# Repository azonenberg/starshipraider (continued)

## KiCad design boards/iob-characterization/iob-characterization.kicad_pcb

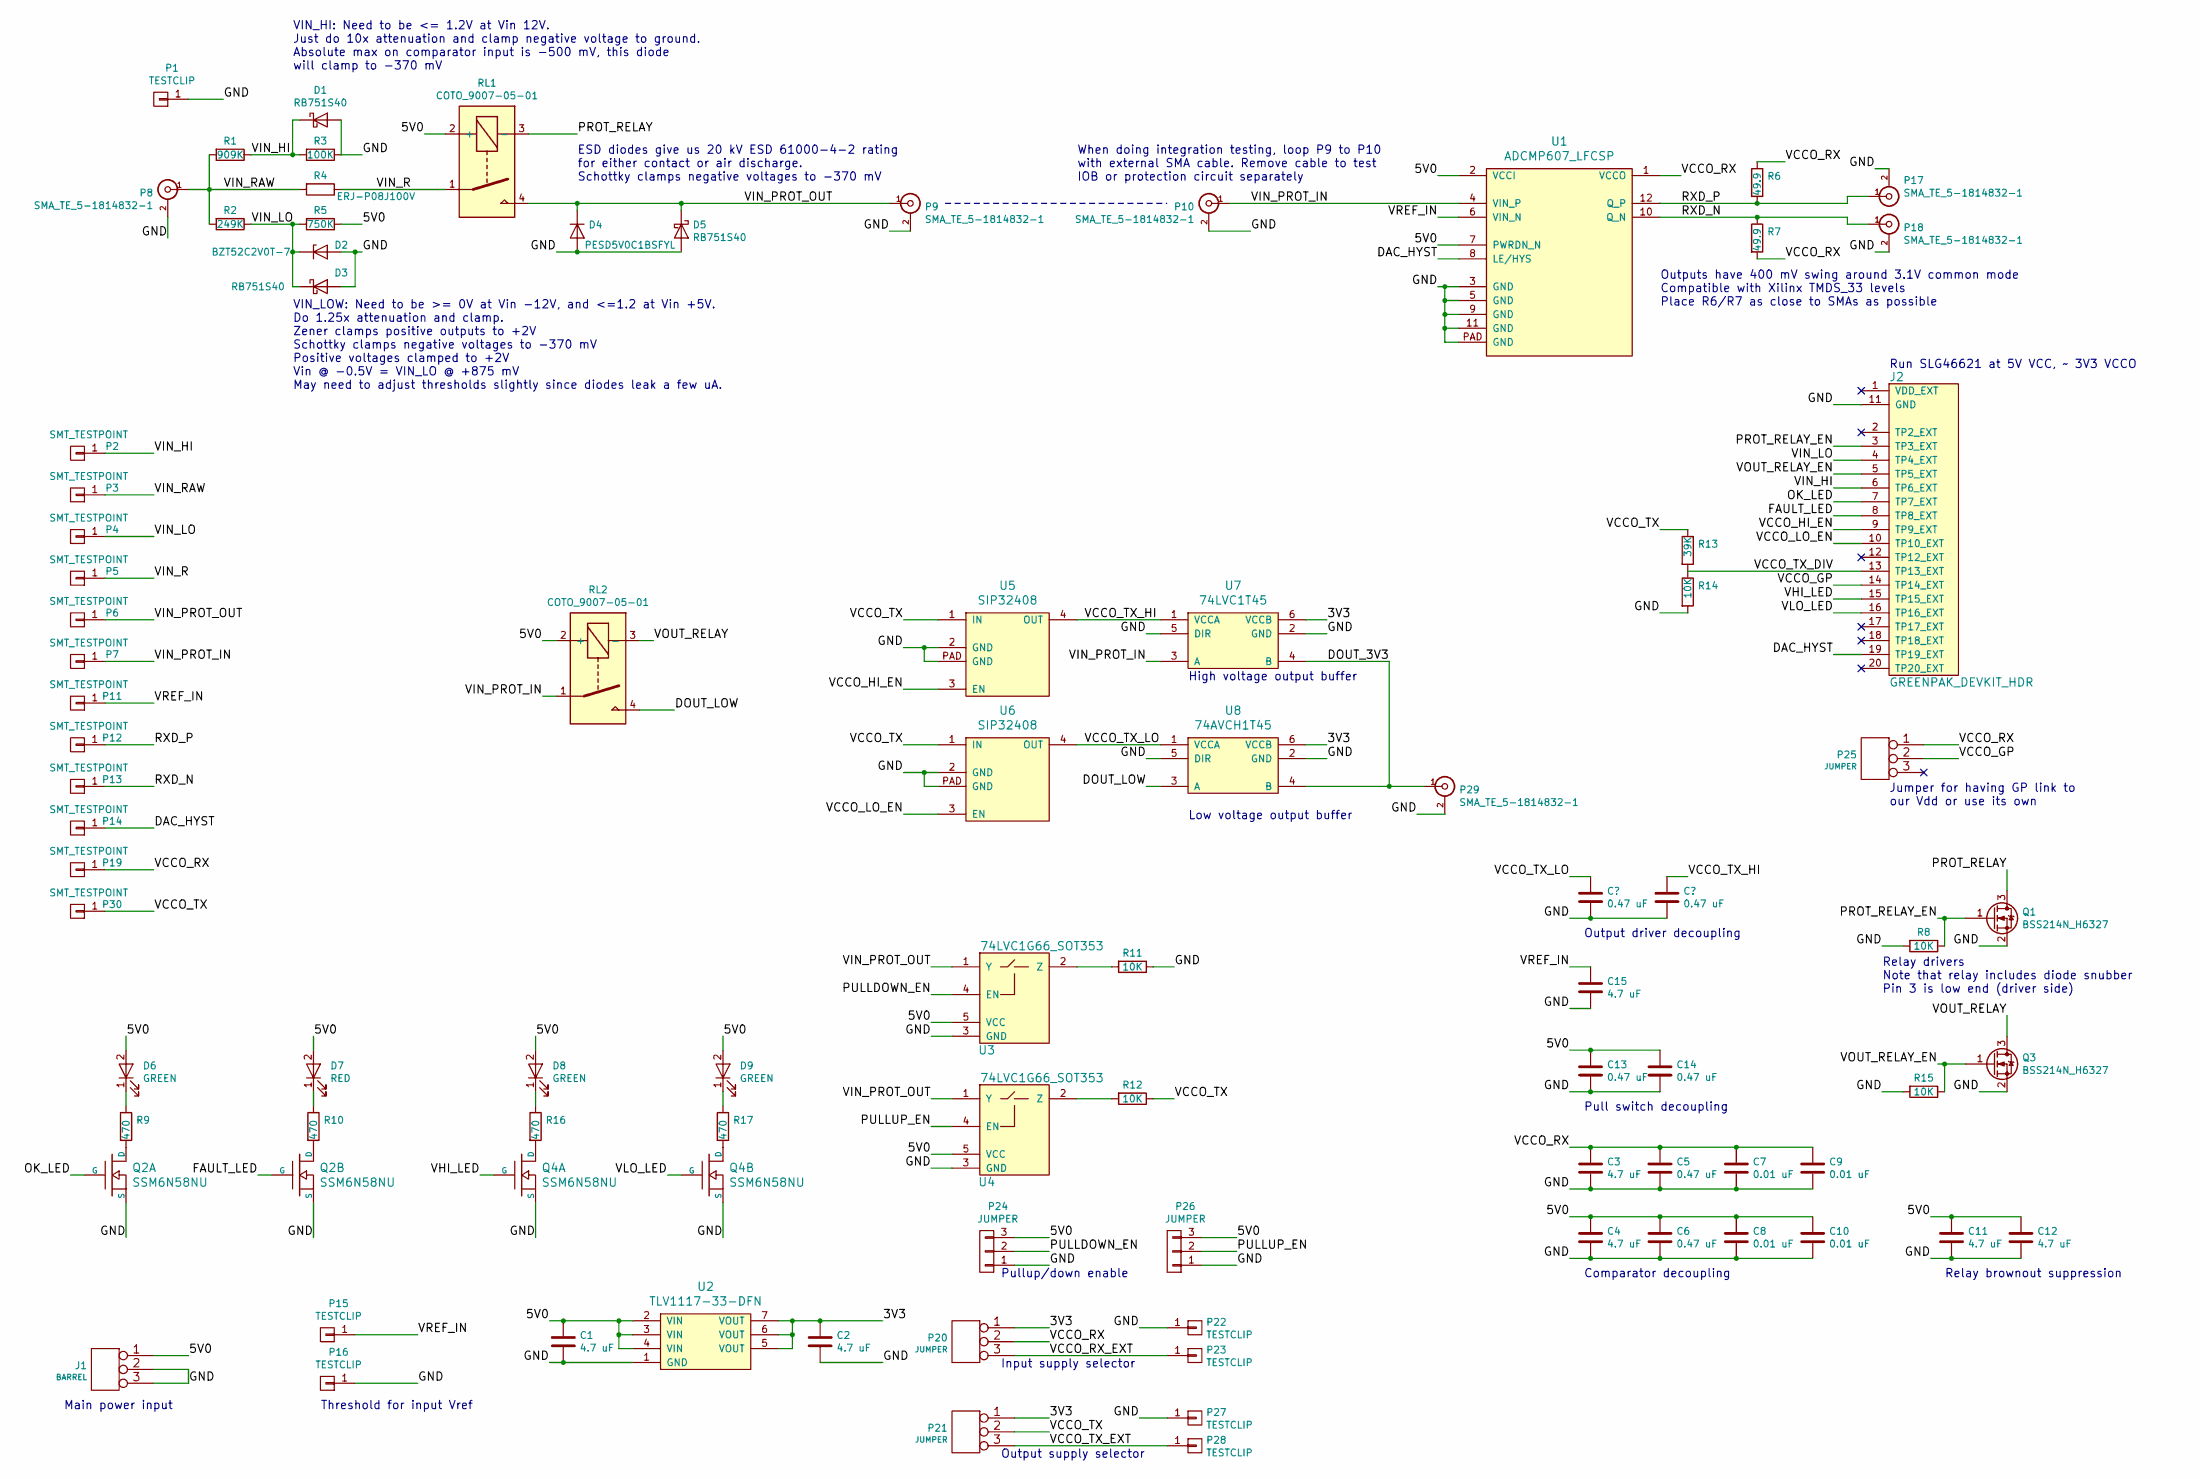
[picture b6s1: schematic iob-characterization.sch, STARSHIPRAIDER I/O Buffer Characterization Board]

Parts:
C1, C2, C3, C4, C11, C12, C15: 4.7 uF; EIA_0603_CAP_NOSILK
C5, C6, C13, C14: 0.47 uF; EIA_0402_CAP_NOSILK
C7, C8, C9, C10: 0.01 uF; EIA_0402_CAP_NOSILK
D1, D3, D5: RB751S40; SOD523F
D2: BZT52C2V0T-7; SOD523
D4: PESD5V0C1BSFYL; SOD962_2
D6, D8, D9: GREEN; EIA_0603_LED
D7: RED; EIA_0603_LED
J1: BARREL; CONN_CUI_PJ-058BH_HIPWR_BARREL_NOSLOT
J2: GREENPAK_DEVKIT_HDR; CONN_HEADER_2.54MM_2x10_RA_FEMALE
P1, P15, P16, P22, P23, P27, P28: TESTCLIP; TESTPOINT_SMT_KEYSTONE_5016
P2, P3, P4, P5, P6, P7, P11, P12, P13, P14, P19, P30: SMT_TESTPOINT; TESTPOINT_SMT_0.5MM
P8, P9, P10, P17, P18, P29: SMA_TE_5-1814832-1; CONN_SMA_PTH
P20, P21, P24, P25, P26: JUMPER; CONN_HEADER_2.54MM_1x3
Q1, Q3: BSS214N_H6327; SOT23_3
Q2, Q4: SSM6N58NU; DFN_6_0.65MM_2x2MM_GDS
R1: 909K; EIA_0402_RES_NOSILK
R2: 249K; EIA_0402_RES_NOSILK
R3: 100K; EIA_0402_RES_NOSILK
R4: ERJ-P08J100V; EIA_1206_CAP_NOSILK
R5: 750K; EIA_0402_RES_NOSILK
R6, R7: 49.9; EIA_0402_RES_NOSILK
R8, R11, R12, R14, R15: 10K; EIA_0402_RES_NOSILK
R9, R10, R16, R17: 470; EIA_0402_RES_NOSILK
R13: 39K; EIA_0402_RES_NOSILK
RL1, RL2: COTO_9007-05-01; RELAY_COTO_9007
U1: ADCMP607_LFCSP; QFN_12_0.5MM_3x3MM
U2: TLV1117-33-DFN; DFN_8_0.8MM_4x4MM
U3, U4: 74LVC1G66_SOT353; SOT353_1
U5, U6: SIP32408; DFN_4_0.5MM_1.6x1.2MM
U7: 74LVC1T45; SOT363
U8: 74AVCH1T45; SOT363

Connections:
/3V3: C2.1, P20.1, P21.1, U2.5 (VOUT), U2.6 (VOUT), U2.7 (VOUT), U7.6 (VCCB), U8.6 (VCCB)
/5V0: C1.1, C4.1, C6.1, C8.1, C10.1, C11.1, C12.1, C13.1, C14.1, D6.2 (A), D7.2 (A), D8.2 (A), D9.2 (A), J1.1, P24.3, P26.3, R5.1, RL1.2 (+), RL2.2 (+), U1.2 (VCCI), U1.7 (PWRDN_N), U2.2 (VIN), U2.3 (VIN), U2.4 (VIN), U3.5 (VCC), U4.5 (VCC)
/DAC_HYST: J2.19 (TP19_EXT), P14.1, U1.8 (LE/HYS)
/DOUT_3V3: P29.1 (In), U7.4 (B), U8.4 (B)
/DOUT_LOW: RL2.4, U8.3 (A)
/FAULT_LED: J2.8 (TP8_EXT), Q2.G2 (G)
/GND: C1.2, C2.2, C3.2, C4.2, C5.2, C6.2, C7.2, C8.2, C9.2, C10.2, C11.2, C12.2, C13.2, C14.2, C15.2, D1.2 (A), D2.2 (A), D3.2 (A), D4.2 (A), D5.2 (A), J1.2 (PM), J1.3, J2.11 (GND), P1.1, P8.2 (Ext), P9.2 (Ext), P10.2 (Ext), P16.1, P17.2 (Ext), P18.2 (Ext), P22.1, P24.1, P26.1, P27.1, P29.2 (Ext), Q1.2 (S), Q2.S1 (S), Q2.S2 (S), Q3.2 (S), Q4.S1 (S), Q4.S2 (S), R3.1, R8.2, R11.1, R14.2, R15.2, U1.3 (GND), U1.5 (GND), U1.9 (GND), U1.11 (GND), U1.PAD (GND), U2.1 (GND), U3.3 (GND), U4.3 (GND), U5.2 (GND), U5.PAD (GND), U6.2 (GND), U6.PAD (GND), U7.2 (GND), U7.5 (DIR), U8.2 (GND), U8.5 (DIR); also elsewhere on the board
/OK_LED: J2.7 (TP7_EXT), Q2.G1 (G)
/PROT_RELAY: Q1.3 (D), RL1.3 (-)
/PROT_RELAY_EN: J2.3 (TP3_EXT), Q1.1 (G), R8.1
/PULLDOWN_EN: P24.2, U3.4 (EN)
/PULLUP_EN: P26.2, U4.4 (EN)
/RXD_N: P13.1, P18.1 (In), R7.1, U1.10 (Q_N)
/RXD_P: P12.1, P17.1 (In), R6.2, U1.12 (Q_P)
/VCCO_GP: J2.14 (TP14_EXT), P25.2 (PM)
/VCCO_HI_EN: J2.9 (TP9_EXT), U5.3 (EN)
/VCCO_LO_EN: J2.10 (TP10_EXT), U6.3 (EN)
/VCCO_RX: C3.1, C5.1, C7.1, C9.1, P19.1, P20.2 (PM), P25.1, R6.1, R7.2, U1.1 (VCCO)
/VCCO_RX_EXT: P20.3, P23.1
/VCCO_TX: P21.2 (PM), P30.1, R12.1, R13.1, U5.1 (IN), U6.1 (IN)
/VCCO_TX_DIV: J2.13 (TP13_EXT), R13.2, R14.1
/VCCO_TX_EXT: P21.3, P28.1
/VCCO_TX_HI: U5.4 (OUT), U7.1 (VCCA); also elsewhere on the board
/VCCO_TX_LO: U6.4 (OUT), U8.1 (VCCA); also elsewhere on the board
/VHI_LED: J2.15 (TP15_EXT), Q4.G1 (G)
/VIN_HI: D1.1 (K), J2.6 (TP6_EXT), P2.1, R1.1, R3.2
/VIN_LO: D2.1 (K), D3.1 (K), J2.4 (TP4_EXT), P4.1, R2.1, R5.2
/VIN_PROT_IN: P7.1, P10.1 (In), RL2.1, U1.4 (VIN_P), U7.3 (A)
/VIN_PROT_OUT: D4.1 (K), D5.1 (K), P6.1, P9.1 (In), RL1.4, U3.1 (Y), U4.1 (Y)
/VIN_R: P5.1, R4.1, RL1.1
/VIN_RAW: P3.1, P8.1 (In), R1.2, R2.2, R4.2
/VLO_LED: J2.16 (TP16_EXT), Q4.G2 (G)
/VOUT_RELAY: Q3.3 (D), RL2.3 (-)
/VOUT_RELAY_EN: J2.5 (TP5_EXT), Q3.1 (G), R15.1
/VREF_IN: C15.1, P11.1, P15.1, U1.6 (VIN_N)
unnamed: D6.1 (K), R9.1
unnamed: D7.1 (K), R10.1
unnamed: D8.1 (K), R16.1
unnamed: D9.1 (K), R17.1
unnamed: Q2.D1 (D), R9.2
unnamed: Q2.D2 (D), R10.2
unnamed: Q4.D1 (D), R16.2
unnamed: Q4.D2 (D), R17.2
unnamed: R11.2, U3.2 (Z)
unnamed: R12.2, U4.2 (Z)

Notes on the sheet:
VIN_HI: Need to be <= 1.2V at Vin 12V. Just do 10x attenuation and clamp negative voltage to ground. Absolute max on comparator input is -500 mV, this diode will clamp to -370 mV
VIN_LOW: Need to be >= 0V at Vin -12V, and <=1.2 at Vin +5V. Do 1.25x attenuation and clamp. Zener clamps positive outputs to +2V Schottky clamps negative voltages to -370 mV Positive voltages clamped to +2V Vin @ -0.5V = VIN_LO @ +875 mV May need to adjust thresholds slightly since diodes leak a f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
ESD diodes give us 20 kV ESD 61000-4-2 rating for either contact or air discharge. Schottky clamps negative voltages to -370 mV
When doing integration testing, loop P9 to P10 with external SMA cable. Remove cable to test IOB or protection circuit separately
Outputs have 400 mV swing around 3.1V common mode Compatible with Xilinx TMDS_33 levels Place R6/R7 as close to SMAs as possible
Main power input
Threshold for input Vref
Run SLG46621 at 5V VCC, ~~ 3V3 VCCO
Jumper for having GP link to our Vdd or use its own
Relay drivers Note that relay includes diode snubber Pin 3 is low end (driver side)
Comparator decoupling
Relay brownout suppression
Output supply selector
Input supply selector
Pullup/down enable
Pull switch decoupling
Low voltage output buffer
High voltage output buffer
Output driver decoupling

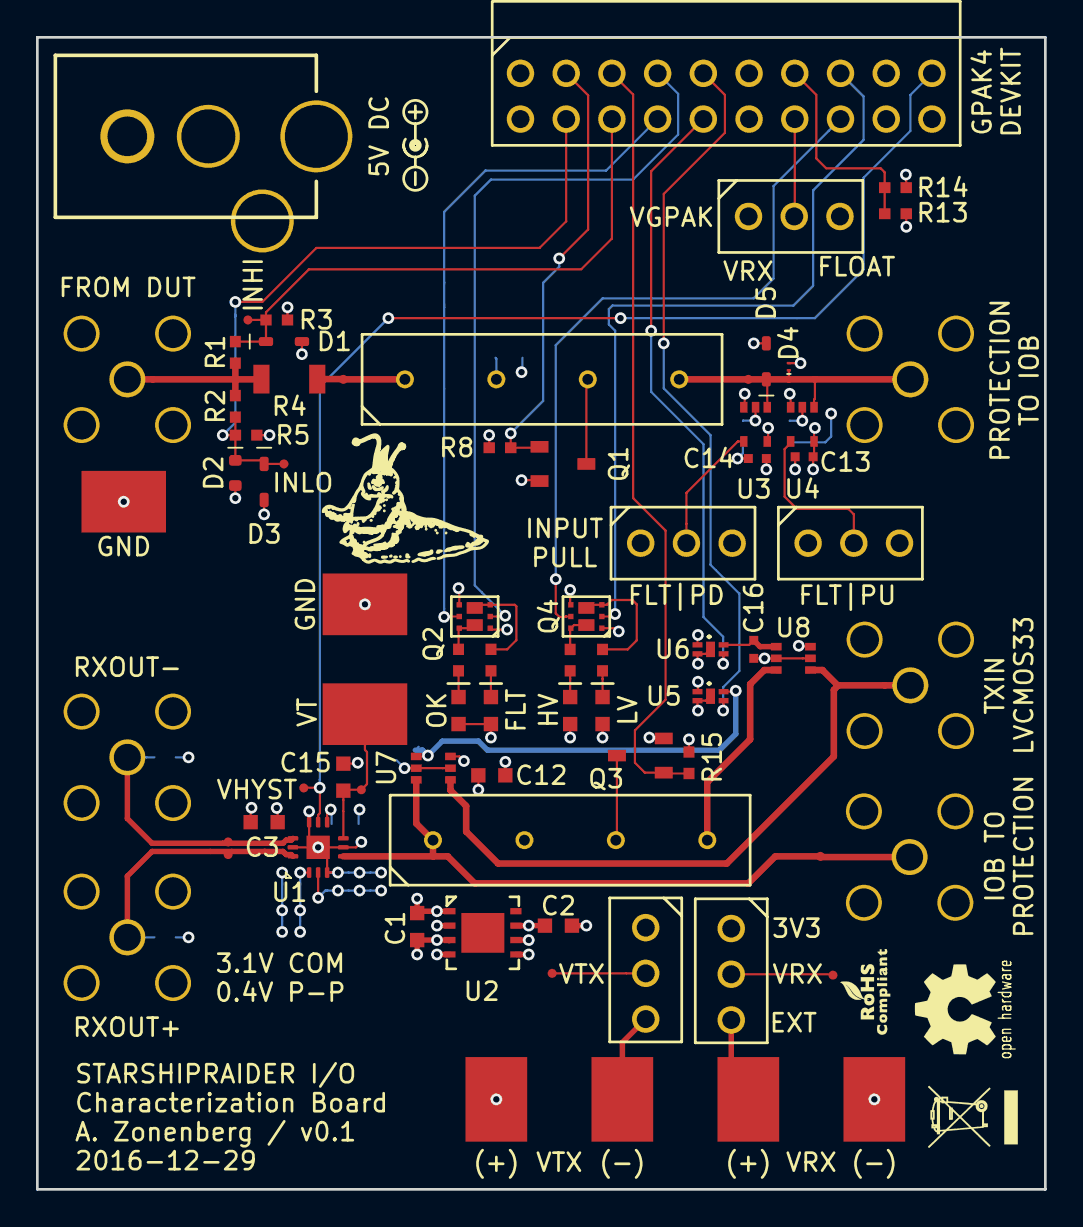
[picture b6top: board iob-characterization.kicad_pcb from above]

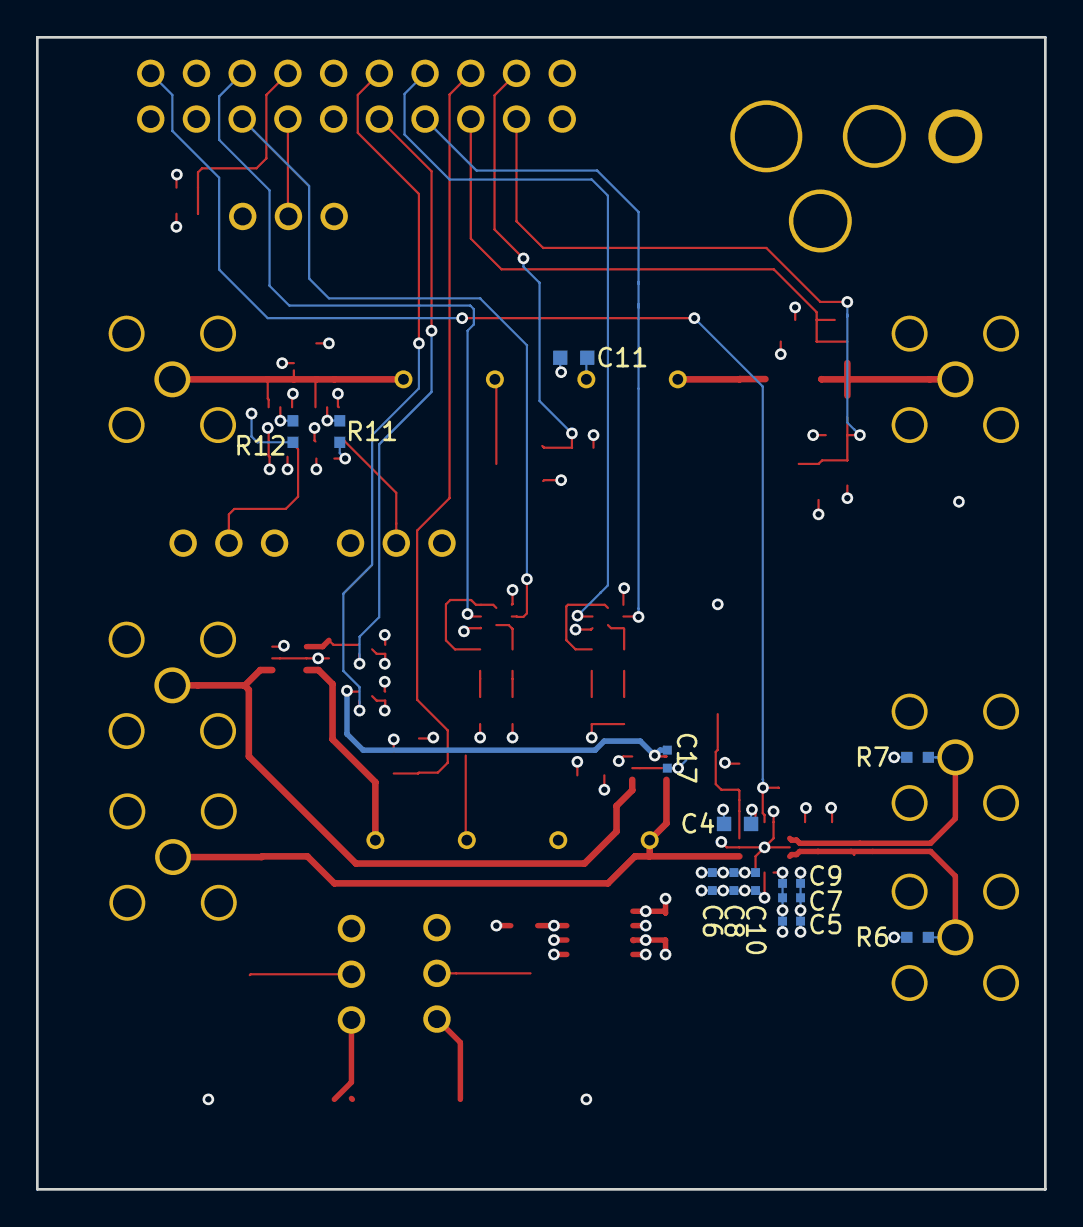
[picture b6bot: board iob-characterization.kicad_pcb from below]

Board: 4 copper layers, 56.0 x 64.0 mm, 89 parts (13 on the bottom side), 45 nets.

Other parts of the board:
C16, C17: 0.47 uF; EIA_0402_CAP_NOSILK

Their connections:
/GND: C16.2, C17.2; also elsewhere on the board
/VCCO_TX_HI: C17.1; also elsewhere on the board
/VCCO_TX_LO: C16.1; also elsewhere on the board

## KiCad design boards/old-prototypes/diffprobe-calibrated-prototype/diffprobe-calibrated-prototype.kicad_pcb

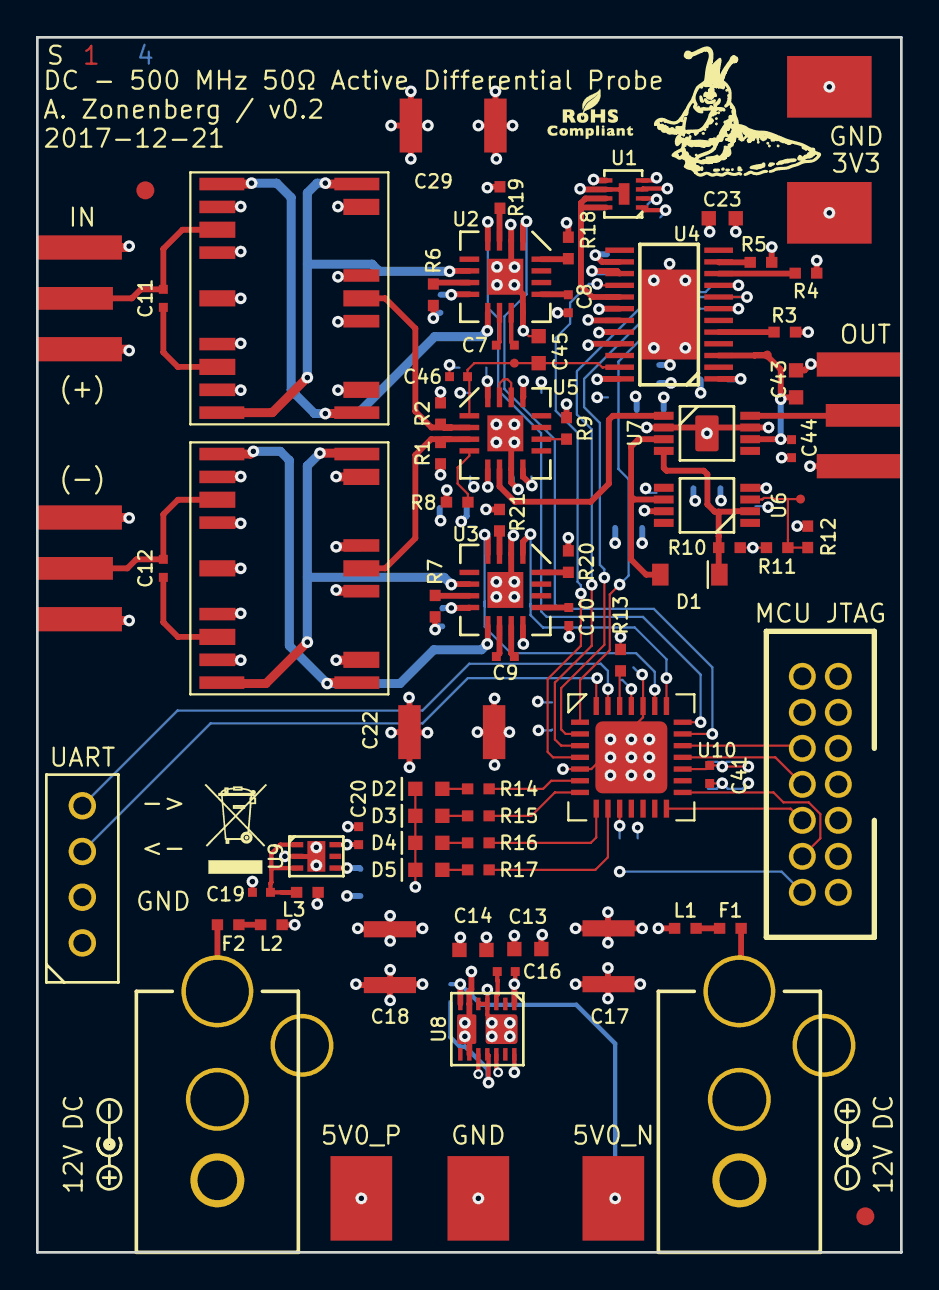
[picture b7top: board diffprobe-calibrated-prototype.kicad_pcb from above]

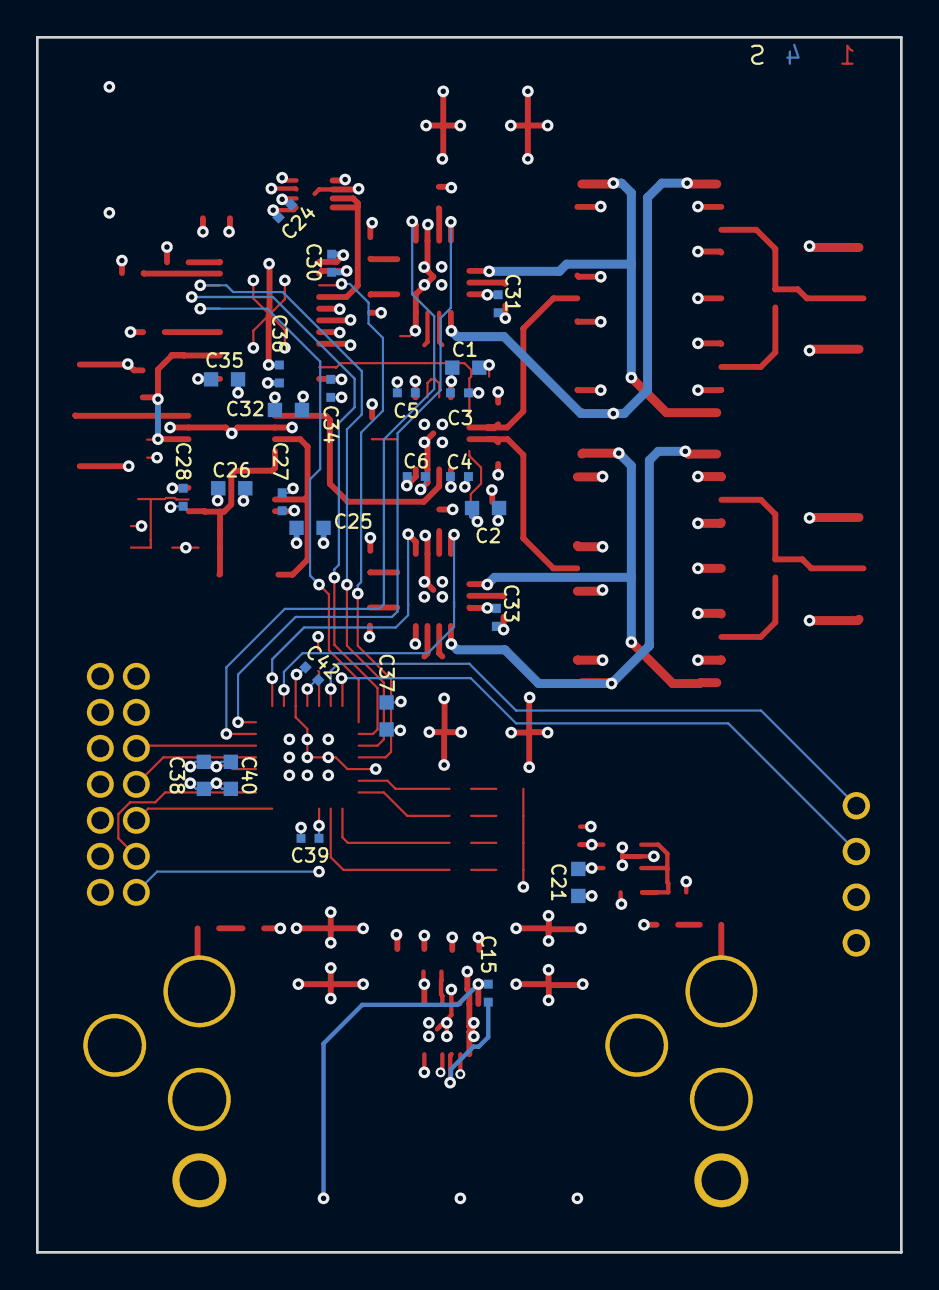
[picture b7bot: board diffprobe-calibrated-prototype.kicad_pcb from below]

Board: 4 copper layers, 48.0 x 67.5 mm, 106 parts (25 on the bottom side), 74 nets.

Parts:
C1, C2, C21, C23, C25, C26, C32, C35, C37, C38, C40, C43, C45: 4.7 uF; EIA_0603_CAP_NOSILK
C3, C4, C5, C6, C24, C27, C28, C30, C34, C36, C39, C41, C42, C44, C46: 0.47 uF; EIA_0402_CAP_NOSILK
C7, C8, C9, C10, C31, C33: 0.1 uF 25V; EIA_0402_CAP_NOSILK
C11, C12, C20: 0.1 uF; EIA_0402_CAP_NOSILK
C13, C14: 4.7 uF 10V; EIA_0603_CAP_NOSILK
C15, C16: 0.01 uF; EIA_0402_CAP_NOSILK
C17, C18: 10 uF 25V; EIA_1210_CAP_NOSILK
C19: 1 uF; EIA_0402_CAP_NOSILK
C22, C29: 22 uF 25V; EIA_1812_CAP_NOSILK
D1: 1N4148; SOD123
D2, D3, D4, D5: GREEN; EIA_0603_LED
F1, F2: 250 mA; EIA_0402_RES_NOSILK
FIDUCIAL_1MM, FIDUCIAL_1MM#2: VAL**; FIDUCIAL_1MM
J1: XILINX_JTAG; XILINX_JTAG_PTH_MOLEX_0878311420
J2, J3: CUI PJ-058BH; CONN_CUI_PJ-058BH_HIPWR_BARREL_NOSLOT
J4, J5, J6: SMA; CONN_SMA_EDGE_SAMTEC_SMA_J_P_H_ST_EM1
J7: CONN_01X04; CONN_HEADER_2.54MM_1x4
K1, K2: AXICOM_HF3_2COIL; RELAY_TE_HF3_2COIL_50OHM
L1, L2, L3: BLM15PX471SN1D; EIA_0402_RES_NOSILK
P4, P5, P6, P7, P8: TESTCLIP; TESTPOINT_SMT_KEYSTONE_5016
R1, R2: 49.9; EIA_0402_RES_NOSILK
R3, R4, R5, R8, R9, R18, R19, R20, R21: 0; EIA_0402_RES_NOSILK
R6, R7: 2; EIA_0402_RES_NOSILK
R10, R11: 3.9K; EIA_0402_RES_NOSILK
R12: 499; EIA_0402_RES_NOSILK
R13: 1K; EIA_0402_RES_NOSILK
R14, R15, R16, R17: 470; EIA_0402_RES_NOSILK
TP1, TP2, TP3: CONN_01X01; TESTPOINT_SMT_0.5MM
U1: MCP1501_DFN; DFN_8_0.5MM_2x2MM
U2, U3: DRV8800_WQFN; QFN_16_0.65MM_4x4MM
U4: AD5752; TSSOP_24_0.65MM_5MM_EPAD_5x3p2
U5: THS3217; QFN_16_0.65MM_4x4MM
U6: AD8675; SOP_8_0.5MM_3MM
U7: HMC346AMS8GE; SOP_8_0.5MM_3MM_EPAD
U8: LT3032IDE-5#PBF; DFN_14_0.5MM_4x3MM_DUALPAD_LTC_DE14MA
U9: MIC5305-33YML; DFN_6_0.65MM_2x2MM
U10: PIC32MM0032GPL028; QFN_28_0.65MM_6x6MM

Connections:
/3V3: C21.1, C23.1, C24.1, C30.1, C37.1, C39.1, C42.1, J1.2, P7.1, R5.1, R13.2, R18.2, R19.2, R20.2, R21.2, U1.1, U1.3, U4.14, U9.4, U10.10, U10.25
/GND: C1.2, C2.1, C3.2, C4.1, C5.2, C6.1, C13.1, C14.2, C17.2, C18.2, C19.2, C20.1, C21.2, C22.2, C23.2, C24.2, C25.2, C26.1, C27.2, C28.1, C29.2, C30.2, C31.2, C32.2, C33.2, C34.2, C35.2, C36.2, C37.2, C38.2, C39.2, C40.2, C41.2, C42.2, C43.2, C44.2, C45.2, C46.2, D2.1, D3.1, D4.1, D5.1, J1.3, J1.5, J1.7, J1.9, J1.11, J2.2, J2.3, J3.2, J3.3, J4.2, J5.2, J6.2, J7.2, K1.2, K1.5, K1.7, K1.10, K1.13, K1.15, K1.17, K1.19, K1.21, K2.2, K2.5, K2.7, K2.10, K2.13, K2.15, K2.17, K2.19, K2.21, P5.1, P8.1, R1.2, R2.1, R3.1, R4.1, R6.2, R7.2, R12.1, U1.2, U1.4, U1.5, U1.6, U1.PAD, U2.2, U2.12, U2.PAD, U3.2, U3.12, U3.PAD, U4.15, U4.18, U4.19, U4.20, U4.21, U5.7, U5.PAD, U7.2, U7.7, U7.PAD, U8.4, U8.5, U8.PADT, U9.2, U9.PAD, U10.5, U10.24, U10.PAD
/Microcontroller/JTAG_TCK: J1.6, U10.14
/Microcontroller/JTAG_TDI: J1.10, U10.19
/Microcontroller/JTAG_TDO: J1.8, U10.18
/Microcontroller/JTAG_TMS: J1.4, U10.15
/Microcontroller/LED0: R14.1, U10.6
/Microcontroller/LED1: R15.1, U10.7
/Microcontroller/LED2: R16.1, U10.8
/Microcontroller/LED3: R17.1, U10.9
/Microcontroller/RELAY1_DIR: U2.1, U10.20
/Microcontroller/RELAY1_EN: U2.4, U10.21
/Microcontroller/RELAY2_DIR: U3.1, U10.22
/Microcontroller/RELAY2_EN: U3.4, U10.23
/Microcontroller/SPI_CS_N: U4.7, U10.1
/Microcontroller/SPI_MISO: U4.16, U10.4
/Microcontroller/SPI_MOSI: U4.9, U10.3
/Microcontroller/SPI_SCK: U4.8, U10.2
/Microcontroller/UART_RX: J7.3, U10.28
/Microcontroller/UART_TX: J7.4, U10.27
/Microcontroller/VCAP: C38.1, C40.1, C41.1, U10.17
/Power Supply/5V0_N: C2.2, C4.2, C6.2, C14.1, C15.2, C26.2, C28.2, C35.1, C36.1, P6.1, R10.2, R11.1, U4.1, U4.PAD, U5.5, U5.8, U6.4, U8.7
/Power Supply/5V0_P: C1.1, C3.1, C5.1, C13.2, C16.2, C25.1, C27.1, C32.1, C34.1, L3.2, P4.1, R8.1, R9.1, U4.24, U5.13, U5.16, U6.7, U8.1
/Power Supply/12V0_N: C18.1, L2.1, U8.6, U8.9, U8.PADB
/Power Supply/12V0_N_UNFUSED: F2.1, J3.1
/Power Supply/12V0_P: C8.2, C10.2, C17.1, C22.1, C29.1, C31.1, C33.1, L1.1, U2.8, U3.8, U8.10, U8.12, U8.14
/Power Supply/12V0_P_UNFUSED: F1.1, J2.1
/Signal Path/2V5_REF: U1.7, U1.8, U4.17
/Signal Path/ATTEN_REF: D1.1, R10.1, U6.2, U7.4
/Signal Path/ATTEN_V2: D1.2, U6.6, U7.3
/Signal Path/COIL1_N: K1.1, K1.12, U2.9
/Signal Path/COIL1_P: K1.11, K1.22, U2.6
/Signal Path/COIL2_N: K2.1, K2.12, U3.9
/Signal Path/COIL2_P: K2.11, K2.22, U3.6
/Signal Path/VATTEN: C43.1, C44.1, TP1.1, U4.3, U7.6
/Signal Path/VATTEN_P: R11.2, R12.2, TP2.1, U6.3
/Signal Path/VIN_N: C12.1, J5.1, K2.14
/Signal Path/VIN_N_AC: C12.2, K2.20
/Signal Path/VIN_N_COUPLED: K2.6, R1.1, U5.3
/Signal Path/VIN_P: C11.1, J4.1, K1.14
/Signal Path/VIN_P_AC: C11.2, K1.20
/Signal Path/VIN_P_COUPLED: K1.6, R2.2, U5.2
/Signal Path/VOFFSET: C45.1, C46.1, TP3.1, U4.23, U5.1
/Signal Path/VOFFSET_BUF: U5.14, U5.15
/Signal Path/VOUT: J6.1, U7.8
/Signal Path/VOUT_RAW: U5.6, U7.1
unnamed: C7.1, U2.10
unnamed: C7.2, U2.11
unnamed: C8.1, U2.13
unnamed: C9.1, U3.10
unnamed: C9.2, U3.11
unnamed: C10.1, U3.13
unnamed: C15.1, U8.11
unnamed: C16.1, U8.3
unnamed: C19.1, L3.1, U9.1, U9.3
unnamed: C20.2, U9.6
unnamed: D2.2, R14.2
unnamed: D3.2, R15.2
unnamed: D4.2, R16.2
unnamed: D5.2, R17.2
unnamed: F1.2, L1.2
unnamed: F2.2, L2.2
unnamed: R3.2, U4.5
unnamed: R4.2, U4.10
unnamed: R5.2, U4.11
unnamed: R6.1, U2.7
unnamed: R7.1, U3.7
unnamed: R8.2, U5.4
unnamed: R9.2, U5.10
unnamed: R13.1, U10.26
unnamed: R18.1, U2.16
unnamed: R19.1, U2.3
unnamed: R20.1, U3.16
unnamed: R21.1, U3.3

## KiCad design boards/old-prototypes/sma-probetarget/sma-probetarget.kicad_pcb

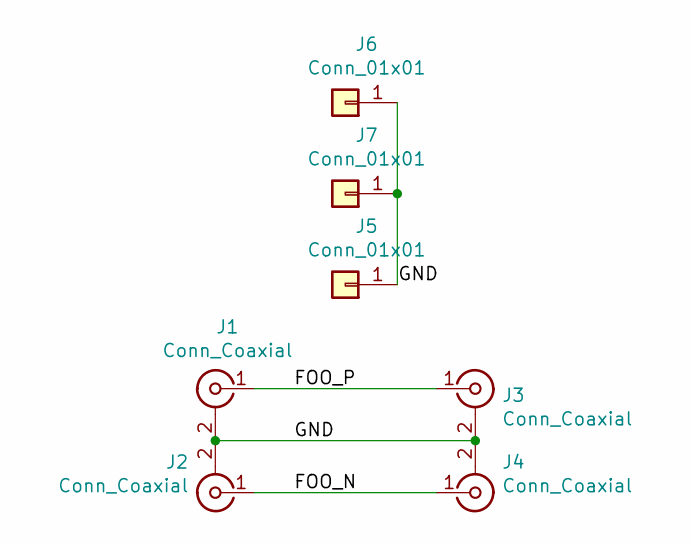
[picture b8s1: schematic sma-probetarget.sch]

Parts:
J1, J2, J3, J4: Conn_Coaxial; CONN_SMA_EDGE_SAMTEC_SMA_J_P_H_ST_EM1
J5: Conn_01x01; TESTPOINT_SMT_KEYSTONE_5016
J6, J7: Conn_01x01; TESTPOINT_BARETRACE_328UM

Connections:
/FOO_N: J2.1 (In), J4.1 (In)
/FOO_P: J1.1 (In), J3.1 (In)
/GND: J1.2 (Ext), J2.2 (Ext), J3.2 (Ext), J4.2 (Ext), J5.1, J6.1, J7.1

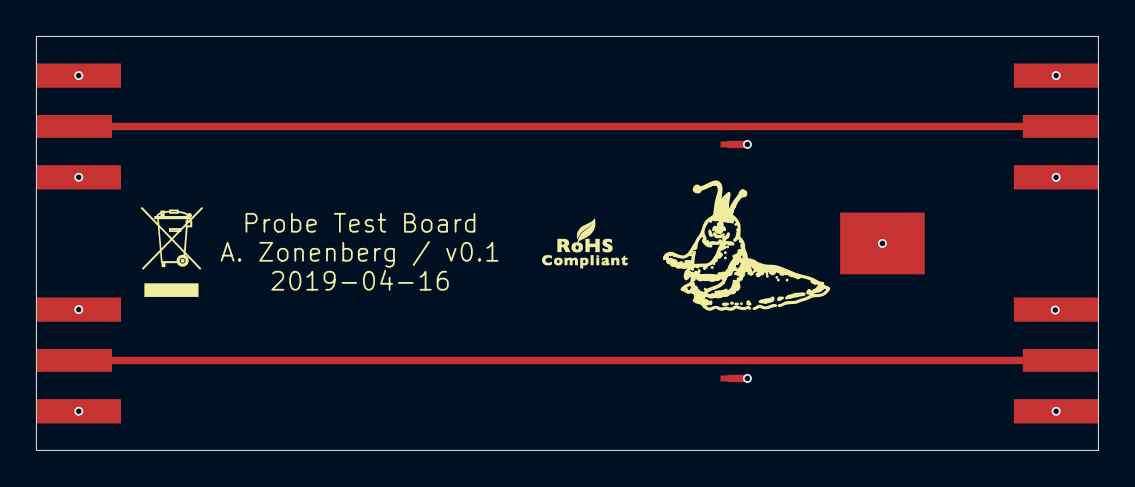
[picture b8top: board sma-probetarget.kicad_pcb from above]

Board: 4 copper layers, 59.0 x 23.0 mm, 7 parts (0 on the bottom side), 3 nets.
